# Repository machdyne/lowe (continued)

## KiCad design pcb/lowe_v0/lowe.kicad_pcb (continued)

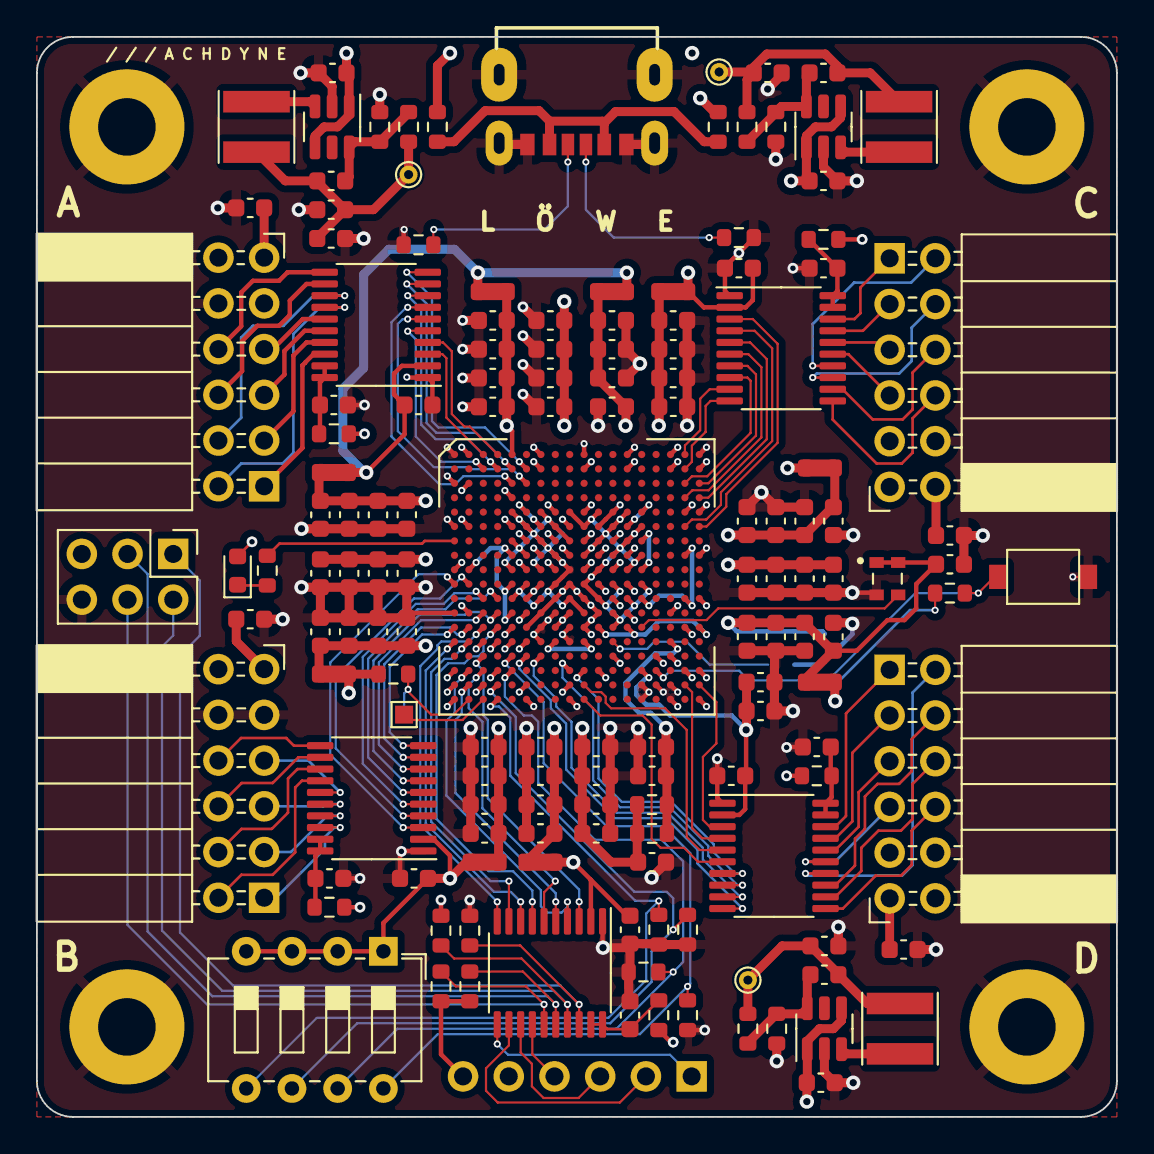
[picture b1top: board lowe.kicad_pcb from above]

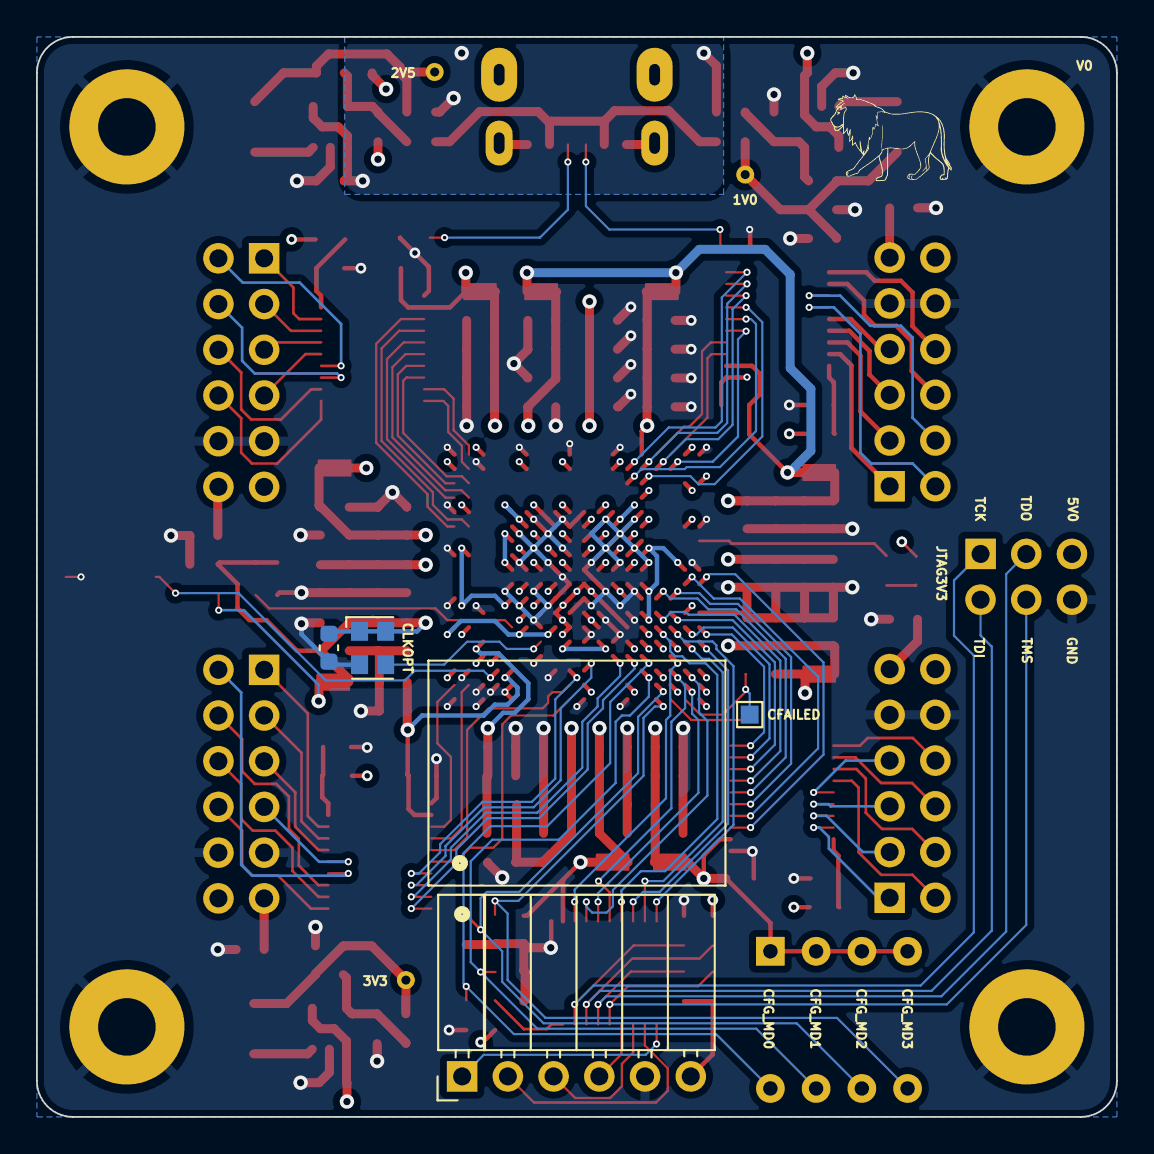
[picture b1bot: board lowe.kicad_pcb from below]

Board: 4 copper layers, 60.0 x 60.0 mm, 153 parts (4 on the bottom side), 120 nets.

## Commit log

2023-10-09 change license to CERN-OHL-P
2023-10-12 add copyright headers
2023-10-12 remove broken tb
